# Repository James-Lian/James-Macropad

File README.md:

# James-Macropad
A functional 3x4 layout macropad created following Hack Club's Hackpad guide. Designed to be used for digital art on Krita. 

## 💡 Features
- 3x4 layout, 12 Cherry MX keys
- rotary encoder
- OLED screen
- custom designed rotary encoder knurled knob
- 5 profiles (default + numpad + art + art-ctrl + art-shift)

## 🔌 PCB
Below is the schematic and PCB.
<br>

## 🧱 Case CAD model
The case is made up of two parts; a top section and a bottom section. The PCB is mounted plateless on the bottom section.    
   
I've also designed a custom knob to fit on the rotary encoder. I've taken inspiration from the knob on alexren's OrpheusPad, while adding some adjustments to ensure that the knob is smaller so it fits better between the rotary encoder and the keycaps.

## 📋 BOM
Here's everything needed to make this hackpad.
- 12x Cherry MX switches
- 12x DSA keycaps
- 6x M3x16mm screws
- 6x M3x5mmx4mm heatset inserts
- 1x 0.91 inch OLED display
- 1x EC11 rotary encoder
- 12x 1N4148 diodes
- 1x unsoldered Seeed XIAO RP2040
- + the custom-designed case (3 printed parts: bottom, top, knob)
 
## ⚙️ Assembly
1. Solder the diodes, Seeeduino, OLED, and rotary encoder to the PCB (recommended in that order)
2. Install CircuitPython on the Seeeduino, and then KMK, as well as the adafruit_display_text, adafruit_framebuf.mpy, adafruit_displayio_ssd1306.mpy, and adafruit_ssd1306.mpy libraries (recommended to do this before the "Middle" 3d printed part blocks the Seeeduino bootloader button)
5. Push the 12 Cherry MX switches through the holes in the "Middle" 3d printed part, and then solder the backs of the switches to the PCB
6. Heatset the inserts into the "Bottom" 3d printed part (4 in total) and install the screws from the top.
<br>

## ⭐ How to Use
Below is a screenshot of the keymap layers (arranged in a 3x4 layout), along with a screenshot of KEY_LABELS that denote what each key does.
<br>
The MO keys temporarily change the macropad's layers when holding them down. The TG keys toggle between the default and art layers. On the art layer (layer 2), holding MO(3) toggles the ART-CTRL layer, essentially acting like a CTRL modifier key and allowing the user to access CTRL-related commands. Holding both the MO(3) and MO(4) keys toggles the ART-CTRL-SHIFT layer, which allows you to access CTRL-SHIFT-related commands and other additional keys. 
<br>

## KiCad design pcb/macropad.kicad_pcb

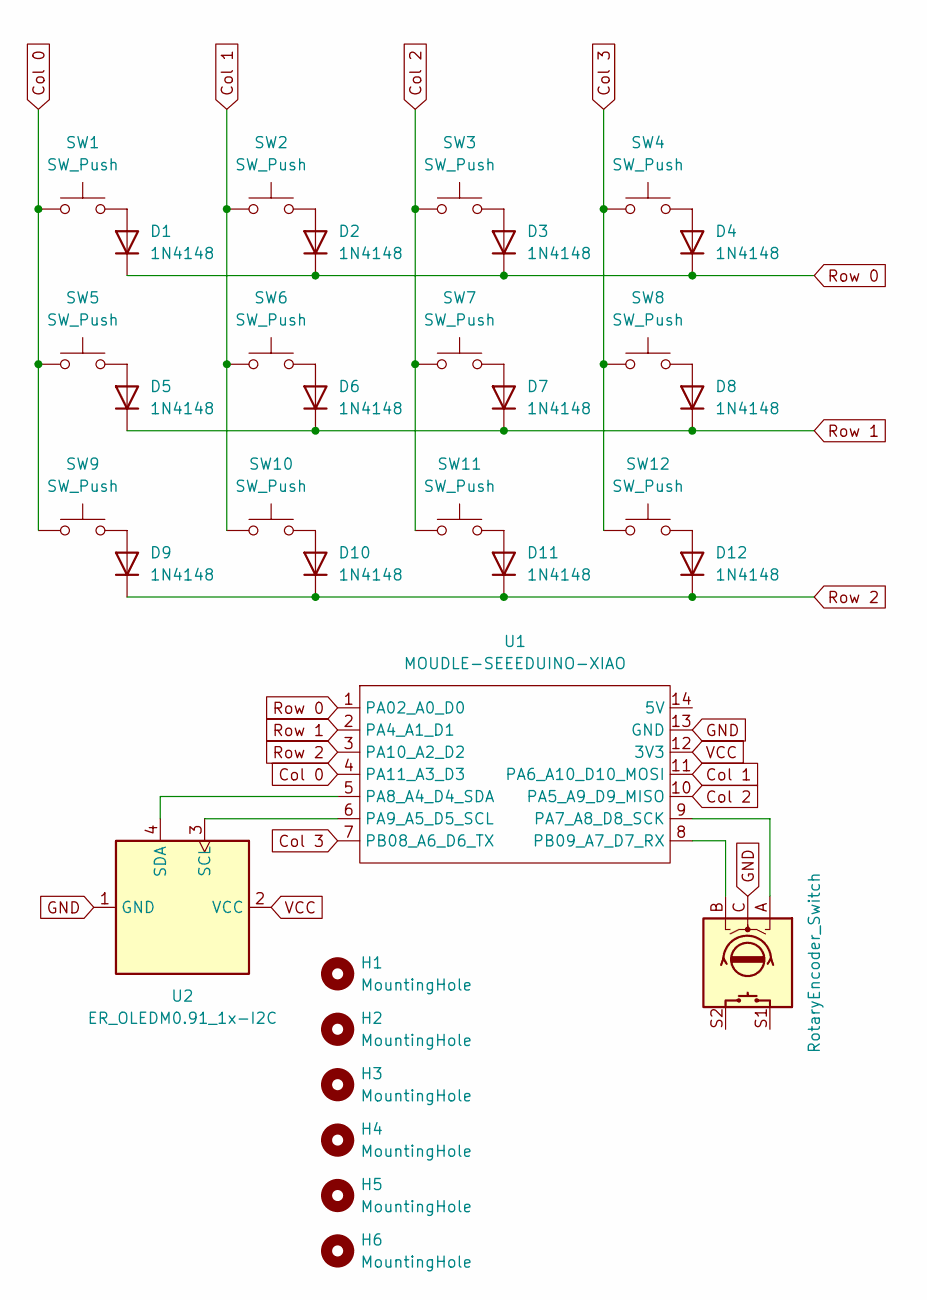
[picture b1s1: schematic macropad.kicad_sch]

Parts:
D1, D2, D3, D4, D5, D6, D7, D8, D9, D10, D11, D12: 1N4148; D_DO-35_SOD27_P7.62mm_Horizontal
H1, H2, H3, H4, H5, H6: MountingHole; MountingHole_3.2mm_M3
SW1, SW2, SW3, SW4, SW5, SW6, SW7, SW8, SW9, SW10, SW11, SW12: SW_Push; SW_Cherry_MX_1.00u_PCB_(3D_STEP)
SW13: RotaryEncoder_Switch; RotaryEncoder_Alps_EC11E-Switch_Vertical_H20mm
U1: MOUDLE-SEEEDUINO-XIAO; XIAO-Generic-Hybrid-14P-2.54-21X17.8MM
U2: ER_OLEDM0.91_1x-I2C; ER_OLEDM0.91_1x-I2C_(3D_STEP)

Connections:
Col 0: SW1.1, SW5.1, SW9.1, U1.4 (PA11_A3_D3)
Col 1: SW2.1, SW6.1, SW10.1, U1.11 (PA6_A10_D10_MOSI)
Col 2: SW3.1, SW7.1, SW11.1, U1.10 (PA5_A9_D9_MISO)
Col 3: SW4.1, SW8.1, SW12.1, U1.7 (PB08_A6_D6_TX)
GND: SW13.C, U1.13 (GND), U2.1 (GND)
unnamed: D1.2 (A), SW1.2
unnamed: D2.2 (A), SW2.2
unnamed: D3.2 (A), SW3.2
unnamed: D4.2 (A), SW4.2
unnamed: D5.2 (A), SW5.2
unnamed: D6.2 (A), SW6.2
unnamed: D7.2 (A), SW7.2
unnamed: D8.2 (A), SW8.2
unnamed: D9.2 (A), SW9.2
unnamed: D10.2 (A), SW10.2
unnamed: D11.2 (A), SW11.2
unnamed: D12.2 (A), SW12.2
unnamed: SW13.A, U1.9 (PA7_A8_D8_SCK)
unnamed: U1.5 (PA8_A4_D4_SDA), U2.4 (SDA)
unnamed: U1.6 (PA9_A5_D5_SCL), U2.3 (SCL)
unnamed: SW13.B, U1.8 (PB09_A7_D7_RX)
Row 0: D1.1 (K), D2.1 (K), D3.1 (K), D4.1 (K), U1.1 (PA02_A0_D0)
Row 1: D5.1 (K), D6.1 (K), D7.1 (K), D8.1 (K), U1.2 (PA4_A1_D1)
Row 2: D9.1 (K), D10.1 (K), D11.1 (K), D12.1 (K), U1.3 (PA10_A2_D2)
VCC: U1.12 (3V3), U2.2 (VCC)

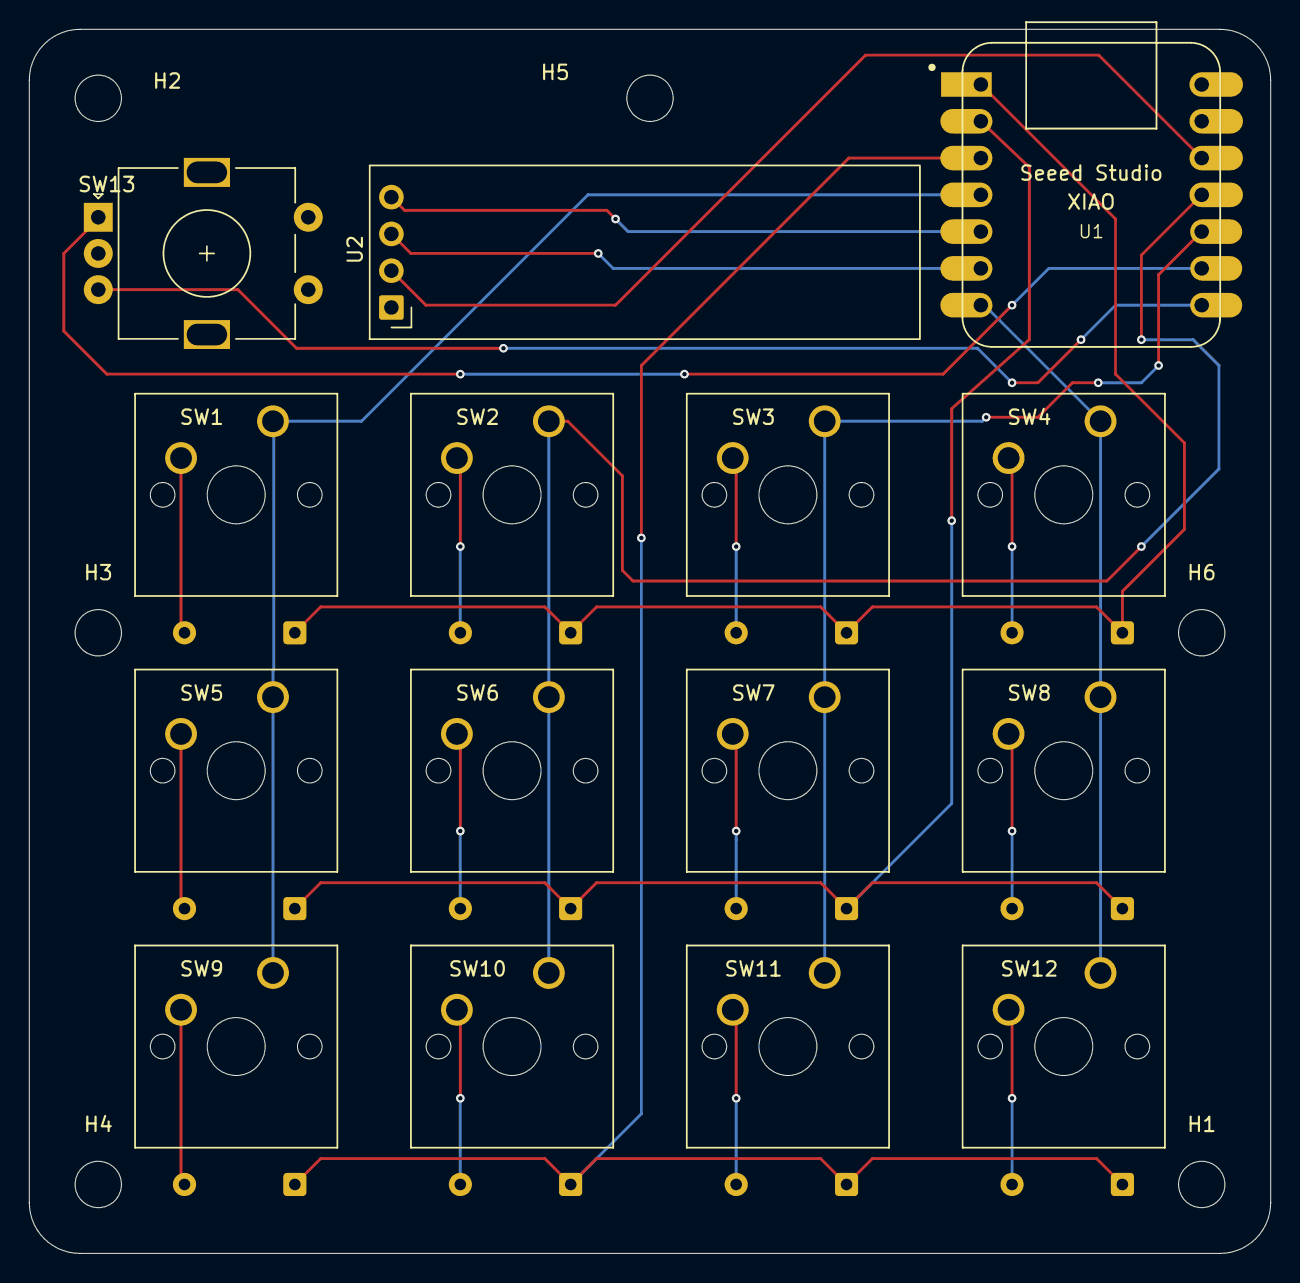
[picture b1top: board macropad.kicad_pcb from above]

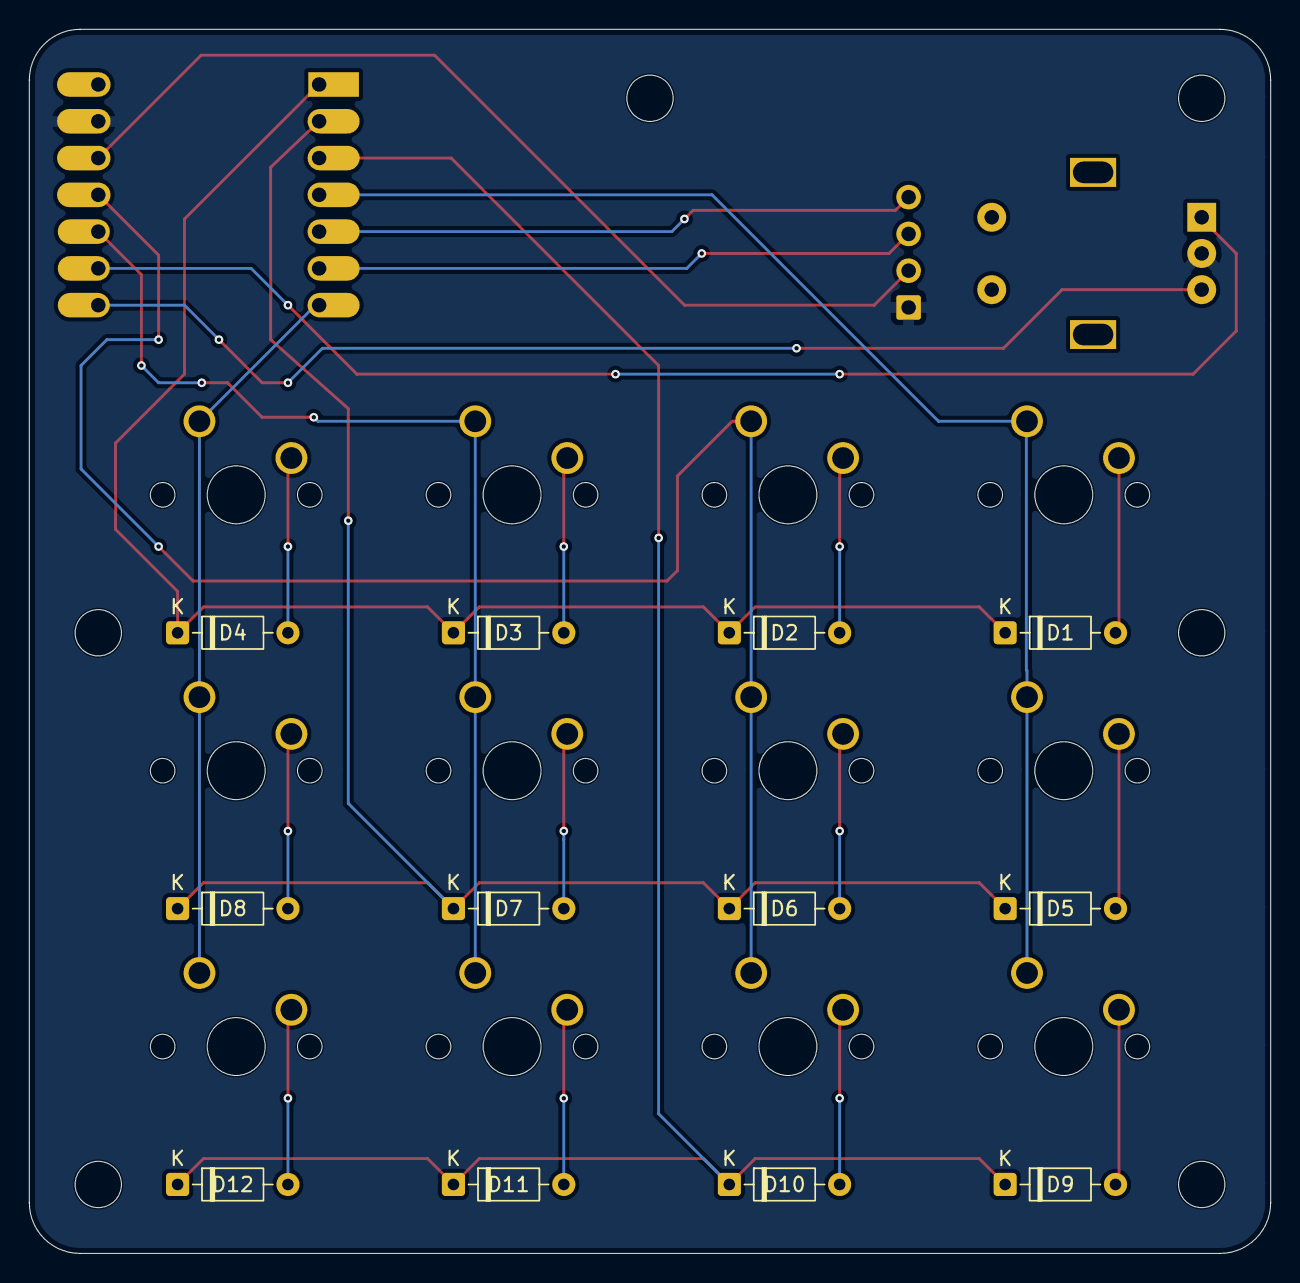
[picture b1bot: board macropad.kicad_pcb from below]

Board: 2 copper layers, 85.7 x 84.5 mm, 33 parts (12 on the bottom side), 25 nets.

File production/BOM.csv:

"Id";"Designator";"Footprint";"Quantity";"Designation";"Supplier and ref";
1;"D1, D2, D3, D4, D5, D6, D7, D8, D9, D10, D11, D12";"D_DO-35_SOD27_P7.62mm_Horizontal";12;"1N4148";;;
2;"SW1, SW2, SW3, SW4, SW5, SW6, SW7, SW8, SW9, SW10, SW11, SW12";"SW_Cherry_MX_1.00u_PCB_(3D_STEP)";12;"SW_Push";;;
3;"SW13";"RotaryEncoder_Alps_EC11E-Switch_Vertical_H20mm";1;"RotaryEncoder_Switch";;;
4;"U1";"XIAO-Generic-Hybrid-14P-2.54-21X17.8MM";1;"MOUDLE-SEEEDUINO-XIAO";;;
5;"U2";"ER_OLEDM0.91_1x-I2C_(3D_STEP)";1;"ER_OLEDM0.91_1x-I2C";;;

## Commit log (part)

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2026-06-27 Initial README commit
2026-06-28 Add CAD .step files
2026-06-28 Complete README for submission
2026-06-28 Add BOM.csv
    Generated from KiCAD.
